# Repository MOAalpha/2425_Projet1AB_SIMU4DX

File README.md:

# 2425_Projet1AB_SIMU4DX
A super nice projet

 L'objectif de ce projet est de reconstituer un simulateur de voiture permettant de ressentir les vraies sensations de conduite, avec un frein à retour de force et 4 pieds movibles.
 
 On s'inspire du projet : https://github.com/ChrGri/DIY-Sim-Racing-FFB-Pedal

 La base ayant déjà été faite, on souhaite modifier le châssis et les pédales de frein afin d'augmenter la sensation de conduire une véritable voiture.

INSTALLER ET FAIRE FONCTIONNER SIMHUB

Tout d'abord, il vous faut installer SimHub sur votre ordinateur.

Cliquez sur "Add/Remove/Features" dans le menu de gauche.

Cliquez sur "addons motion" pour activer le contrôle de mouvement.

Normalement, "Motion" apparaît sur SimHub (icône avec un siège).

Cliquez sur "Let's test it".

Choisissez comme configuration "3 DOFs, 2 fronts, 1 rear".

Cliquez sur "Add new controller".

Choisissez "generic serial output"

Dans "Connexion", assurez-vous que votre carte est connectée sur le bon COM.

Vous pouvez régler la dimension de la plateforme ce qui vous permet d'obtenir la limitation des axes.

Cliquez ensuite sur "Edit serial commands setting".

Dans cet onglet, vous voyez le type de données que SimHub vous envoie : ce sont deux angles (le roll et le pitch) et une translation selon l'axe horizontal qui est appelé "heave".

C'est dans cet onglet que vous pouvez régler la forme des données que vous souhaitez envoyer :

Baudrate: 115000

Data bits: 8

Stop bits: 1

Parity: none

Number of controlled axis: 3

Axis output format: decimal

Axis resolution: 8 bits (donc de 0 à 255)

Motion update commands: <axis1> <axis2> <axis3> (à copier-coller ; vous pouvez aussi cliquer sur les "..." pour les ajouter)

Cliquez sur "Edit axis assignment". Vous n'avez que trois axes (rear center, front left corner, front right corner). Vous pouvez tester l'envoi des données dans cet onglet.

LIRE LES DONNÉES DE SIMHUB

Méthode avec deux STM32 :

Nous avons utilisé cette méthode au début de notre projet, car nous n'avions pas encore terminé l'impression des cartes.

Si vous disposez de deux microcontrôleurs STM32 ayant l'UART 1 et 2, il vous suffit de relier les ports RX, TX et GND de vos deux cartes STM32.

Par la suite, il vous faut installer STM32CubeIDE et PuTTY. Activez l'UART 1 et 2. Puis, ajoutez cette ligne de code qui vous permettra de lire les données.

Une fois que le code est chargé dans les deux cartes, il faut par la suite ouvrir PuTTY et SimHub.

Dans SimHub : Il faut revenir dans l'onglet "Edit axis assignment" et cliquer sur le bouton de test pour que SimHub envoie les données.

Dans PuTTY : Cliquez sur "Connexion type" "Serial", puis choisissez le COM correspondant à votre carte et sélectionnez 115200 bauds.

Méthode avec le hub USB :

Cette méthode permet de tester le fonctionnement du hub USB.

La carte qui reçoit les données est le hub USB dans notre schéma d'architecture ; elle reçoit les données via le port USB. Il faut relier l'un des ports USB du hub USB dédié aux autres cartes vers le PC. Ensuite, vous pourrez lire les données envoyées avec PuTTY. Malheureusement, nous n'avons pas pu le faire, car nous avons rencontré un problème avec le timer de notre microcontrôleur.

 On a effectué une PCB de communication : 
 
 Elle a pour rôle la transmission des infos du jeu prélevés à l'aide de simhub aux 4 moteurs qui font bouger le châssis.

 NB : Le circuit semble correct (On a bien 5V en entrée du régulateur et 3.3V en sortie) MAIS son horloge interne ne fonctionne pas.

 On a effectué une PCB Moteur pour chacun des 4 moteurs : 

Celle-ci se charge d'indiquer au driver à quel point il faut bouger le vérin.

A suivre : 

Tester la PCB du STEPPER pour commander la pédale de frein avec retour de force. \
 \
Assembler le tout. \
Profiter des sensations.

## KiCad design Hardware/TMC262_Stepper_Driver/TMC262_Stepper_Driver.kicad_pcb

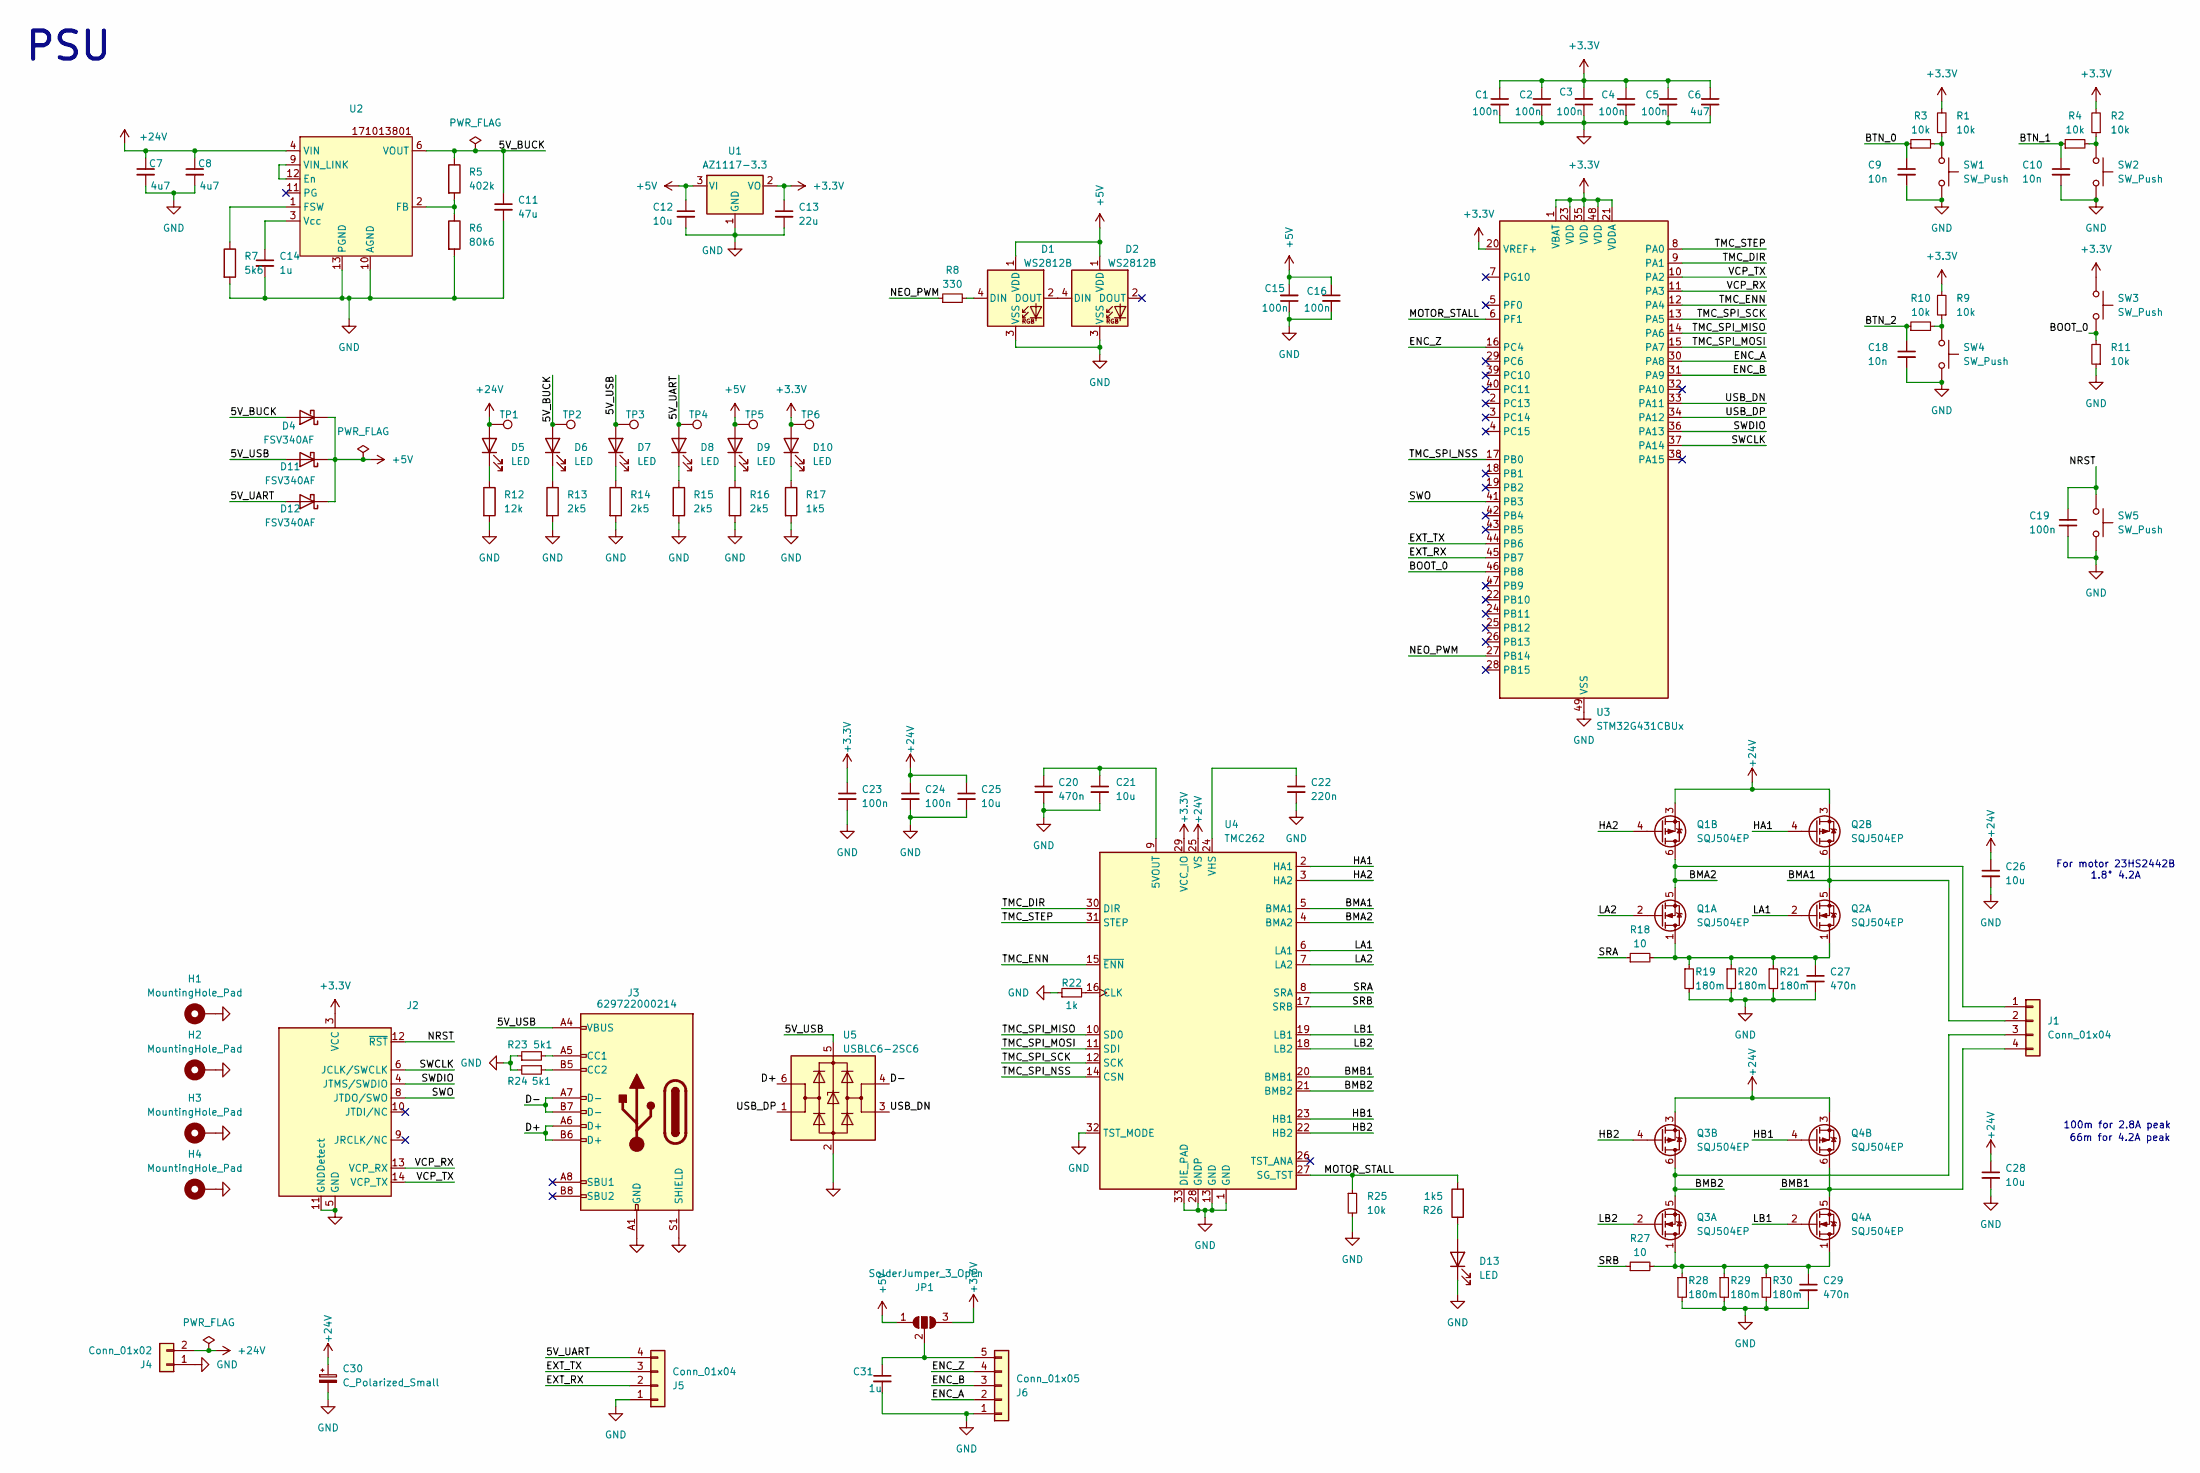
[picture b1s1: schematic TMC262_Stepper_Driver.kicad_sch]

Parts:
C1, C2, C3, C4, C5, C15, C16, C23, C24: 100n; C_0402_1005Metric
C6: 4u7; C_0402_1005Metric
C7, C8: 4u7; C_1210_3225Metric; MPN 885012209048
C9, C10, C18: 10n; C_0402_1005Metric; MPN WE 885012205050
C11: 47u; C_0805_2012Metric; MPN 885 012 107 006
C12, C21: 10u; C_0603_1608Metric; MPN 885 012 106 006
C13: 22u; C_0805_2012Metric; MPN 885 012 107 011
C14, C31: 1u; C_0402_1005Metric
C19: 100n; C_0402_1005Metric; MPN WE 885012205050
C20, C27, C29: 470n; C_0402_1005Metric
C22: 220n; C_0402_1005Metric
C25, C26, C28: 10u; C_1206_3216Metric; MPN 885 012 208 069
C30: C_Polarized_Small; CP_Elec_10x10.5; MPN 865060657012
D1, D2: WS2812B; LED_WS2812B_PLCC4_5.0x5.0mm_P3.2mm
D4, D11, D12: FSV340AF; D_SMA
D5, D6, D7, D8, D9, D10, D13: LED; LED_0603_1608Metric
H1, H2, H3, H4: MountingHole_Pad; MountingHole_3.2mm_M3_Pad_Via
J1: Conn_01x04; JST_XH_B4B-XH-A_1x04_P2.50mm_Vertical
J2: PinHeader_2x07_P1.27mm_Vertical_SMD
J3: 629722000214; USB_C_Receptacle_HRO_TYPE-C-31-M-12; MPN 629722000214
J4: Conn_01x02; AMASS_XT30U-M_1x02_P5.0mm_Vertical
J5: Conn_01x04; JST_PH_B4B-PH-K_1x04_P2.00mm_Vertical
J6: Conn_01x05; JST_PH_B5B-PH-K_1x05_P2.00mm_Vertical
JP1: SolderJumper_3_Open; SolderJumper-3_P2.0mm_Open_TrianglePad1.0x1.5mm
Q1, Q2, Q3, Q4: SQJ504EP; MPN SQJ504EP-T1_GE3
R1, R2, R3, R4, R9, R10, R11, R25: 10k; R_0402_1005Metric
R5: 402k; R_0402_1005Metric
R6: 80k6; R_0402_1005Metric
R7: 5k6; R_0402_1005Metric
R8: 330; R_0402_1005Metric
R12: 12k; R_0402_1005Metric
R13, R14, R15, R16: 2k5; R_0402_1005Metric
R17, R26: 1k5; R_0402_1005Metric
R18, R27: 10; R_0402_1005Metric
R19, R20, R21, R28, R29, R30: 180m; R_0612_1632Metric; MPN 561 070 332 057
R22: 1k; R_0402_1005Metric
R23, R24: 5k1; R_0402_1005Metric
SW1, SW2, SW3, SW4, SW5: SW_Push; KSS221GLFS; MPN KSS221GLFS
TP1: 24V; TestPoint_Pad_D1.0mm
TP2: 5V_BUCK; TestPoint_Pad_D1.0mm
TP3, TP4: 5V_USB; TestPoint_Pad_D1.0mm
TP5: 5V; TestPoint_Pad_D1.0mm
TP6: 3V3; TestPoint_Pad_D1.0mm
U1: AZ1117-3.3; SOT-223
U2: 171013801
U3: STM32G431CBUx; QFN-48-1EP_7x7mm_P0.5mm_EP5.6x5.6mm
U4: TMC262; QFN-32-1EP_5x5mm_P0.5mm_EP3.45x3.45mm
U5: USBLC6-2SC6; SOT-23-6; MPN USBLC6-2SC6

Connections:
+3.3V: C1.1, C2.1, C3.2, C4.1, C5.1, C6.1, C13.1, C23.1, D10.2 (A), J2.3 (VCC), JP1.3 (B), R1.2, R2.2, R9.2, SW3.1, TP6.1, U1.2 (VO), U1.4 (VO), U3.1 (VBAT), U3.20 (VREF+), U3.21 (VDDA), U3.23 (VDD), U3.35 (VDD), U3.48 (VDD), U4.29 (VCC_IO)
+5V: C12.1, C15.2, C16.1, D1.1 (VDD), D2.1 (VDD), D4.1 (K), D9.2 (A), D11.1 (K), D12.1 (K), JP1.1 (A), TP5.1, U1.3 (VI)
+24V: C7.1, C8.1, C24.1, C25.1, C26.1, C28.1, C30.1, D5.2 (A), J4.2, Q1.3 (1), Q2.3 (1), Q3.3 (1), Q4.3 (1), TP1.1, U2.4 (VIN), U2.5 (VIN), U4.25 (VS)
/5V_BUCK: C11.1, D4.2 (A), D6.2 (A), R5.1, TP2.1, U2.6 (VOUT), U2.7 (VOUT)
/5V_UART: D8.2 (A), D12.2 (A), J5.4, TP4.1
/5V_USB: D7.2 (A), D11.2 (A), J3.A4 (VBUS), J3.A9 (VBUS), J3.B4 (VBUS), J3.B9 (VBUS), TP3.1, U5.5 (VBUS)
/BMA1: J1.2, Q2.5 (D), Q2.6 (D), U4.5 (BMA1)
/BMA2: J1.1, Q1.5 (D), Q1.6 (D), U4.4 (BMA2)
/BMB1: J1.4, Q4.5 (D), Q4.6 (D), U4.20 (BMB1)
/BMB2: J1.3, Q3.5 (D), Q3.6 (D), U4.21 (BMB2)
/BOOT_0: R11.2, SW3.2, U3.46 (PB8)
/BTN_0: C9.1, R3.1
/BTN_1: C10.1, R4.1
/BTN_2: C18.1, R10.1
/D+: J3.A6 (D+), J3.B6 (D+), U5.6 (I/O1)
/D-: J3.A7 (D-), J3.B7 (D-), U5.4 (I/O2)
/ENC_A: J6.2, U3.30 (PA8)
/ENC_B: J6.3, U3.31 (PA9)
/ENC_Z: J6.4, U3.16 (PC4)
/EXT_RX: J5.2, U3.45 (PB7)
/EXT_TX: J5.3, U3.44 (PB6)
/HA1: Q2.4 (G), U4.2 (HA1)
/HA2: Q1.4 (G), U4.3 (HA2)
/HB1: Q4.4 (G), U4.23 (HB1)
/HB2: Q3.4 (G), U4.22 (HB2)
/LA1: Q2.2 (G), U4.6 (LA1)
/LA2: Q1.2 (G), U4.7 (LA2)
/LB1: Q4.2 (G), U4.19 (LB1)
/LB2: Q3.2 (G), U4.18 (LB2)
/MOTOR_STALL: R25.1, R26.2, U3.6 (PF1), U4.27 (SG_TST)
/NEO_PWM: R8.1, U3.27 (PB14)
/NRST: C19.1, J2.12 (~RST), SW5.1
/SRA: R18.1, U4.8 (SRA)
/SRB: R27.1, U4.17 (SRB)
/SWCLK: J2.6 (JCLK/SWCLK), U3.37 (PA14)
/SWDIO: J2.4 (JTMS/SWDIO), U3.36 (PA13)
/SWO: J2.8 (JTDO/SWO), U3.41 (PB3)
/TMC_DIR: U3.9 (PA1), U4.30 (DIR)
/TMC_ENN: U3.12 (PA4), U4.15 (~ENN)
/TMC_SPI_MISO: U3.14 (PA6), U4.10 (SD0)
/TMC_SPI_MOSI: U3.15 (PA7), U4.11 (SDI)
/TMC_SPI_NSS: U3.17 (PB0), U4.14 (CSN)
/TMC_SPI_SCK: U3.13 (PA5), U4.12 (SCK)
/TMC_STEP: U3.8 (PA0), U4.31 (STEP)
/USB_DN: U3.33 (PA11), U5.3 (I/O2)
/USB_DP: U3.34 (PA12), U5.1 (I/O1)
/VCP_RX: J2.13 (VCP_RX), U3.11 (PA3)
/VCP_TX: J2.14 (VCP_TX), U3.10 (PA2)
GND: C1.2, C2.2, C3.1, C4.2, C5.2, C6.2, C7.2, C8.2, C9.2, C10.2, C11.2, C12.2, C13.2, C14.2, C15.1, C16.2, C18.2, C19.2, C20.2, C21.2, C22.2, C23.2, C24.2, C25.2, C26.2, C27.2, C28.2, C29.2, C30.2, C31.2, D1.3 (VSS), D2.3 (VSS), D13.1 (K), H1.1, H2.1, H3.1, H4.1, J2.5 (GND), J2.7 (GND), J2.11 (GNDDetect), J3.A1 (GND), J3.A12 (GND), J3.B1 (GND), J3.B12 (GND), J3.S1 (SHIELD), J4.1, J5.1, J6.1, R6.2, R7.2, R11.1, R12.2, R13.2, R14.2, R15.2, R16.2, R17.2, R19.2, R20.2, R21.2, R22.1, R23.1, R24.2, R25.2, R28.2, R29.2, R30.2, SW1.2, SW2.2, SW4.2, SW5.2, U1.1 (GND), U2.10 (AGND), U2.13 (PGND), U3.49 (VSS), U4.1 (GND), U4.13 (GND), U4.28 (GNDP), U4.32 (TST_MODE), U4.33 (DIE_PAD), U5.2 (GND)
unnamed: D1.4 (DIN), R8.2
unnamed: D1.2 (DOUT), D2.4 (DIN)
unnamed: D5.1 (K), R12.1
unnamed: D6.1 (K), R13.1
unnamed: D7.1 (K), R14.1
unnamed: D8.1 (K), R15.1
unnamed: D9.1 (K), R16.1
unnamed: D10.1 (K), R17.1
unnamed: D13.2 (A), R26.1
unnamed: J3.A5 (CC1), R23.2
unnamed: J3.B5 (CC2), R24.1
unnamed: C31.1, J6.5, JP1.2 (C)
unnamed: C27.1, Q1.1 (S), Q2.1 (S), R18.2, R19.1, R20.1, R21.1
unnamed: C29.1, Q3.1 (S), Q4.1 (S), R27.2, R28.1, R29.1, R30.1
unnamed: R1.1, R3.2, SW1.1
unnamed: R2.1, R4.2, SW2.1
unnamed: R9.1, R10.2, SW4.1
unnamed: U2.9 (VIN_LINK), U2.12 (En)
unnamed: R5.2, R6.1, U2.2 (FB)
unnamed: R7.1, U2.1 (FSW)
unnamed: C14.1, U2.3 (Vcc)
unnamed: C20.1, C21.1, U4.9 (5VOUT)
unnamed: R22.2, U4.16 (CLK)
unnamed: C22.1, U4.24 (VHS)

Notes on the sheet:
66m for 4.2A peak
100m for 2.8A peak
For motor 23HS2442B 1.8° 4.2A
PSU

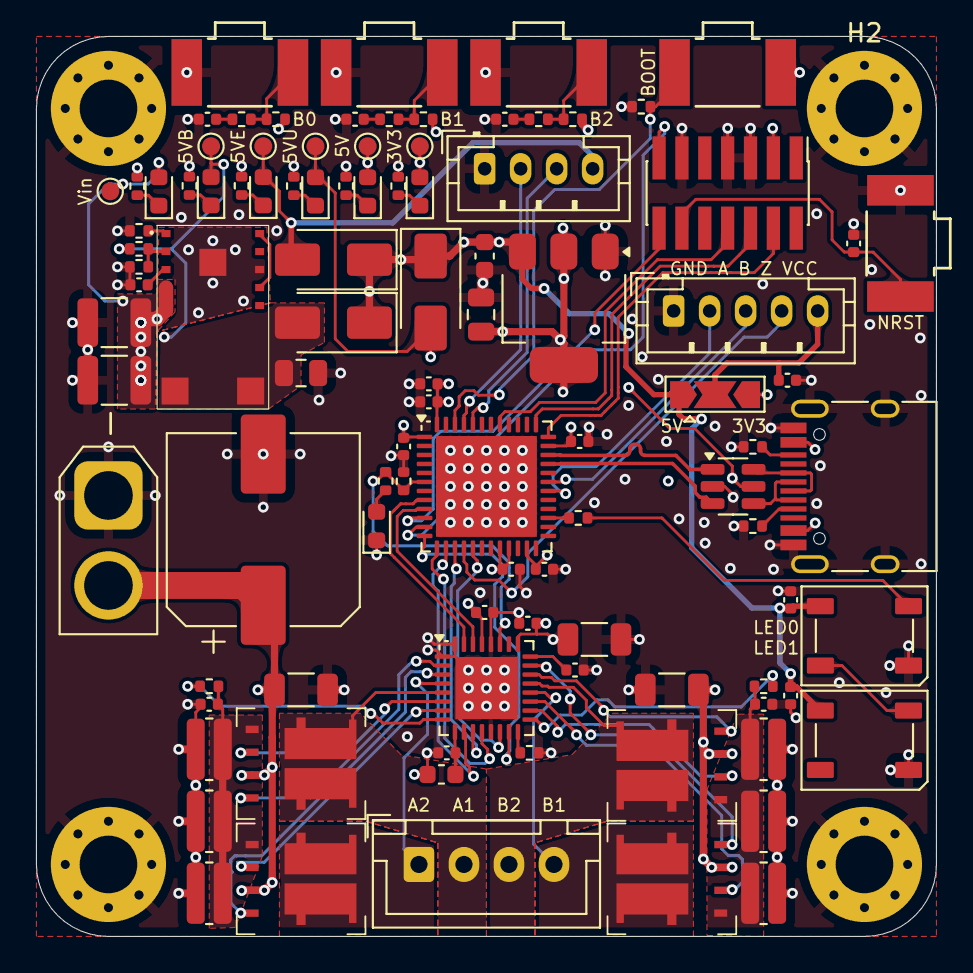
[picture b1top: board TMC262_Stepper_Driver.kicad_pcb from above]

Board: 4 copper layers, 50.0 x 50.0 mm, 103 parts (0 on the bottom side), 73 nets.

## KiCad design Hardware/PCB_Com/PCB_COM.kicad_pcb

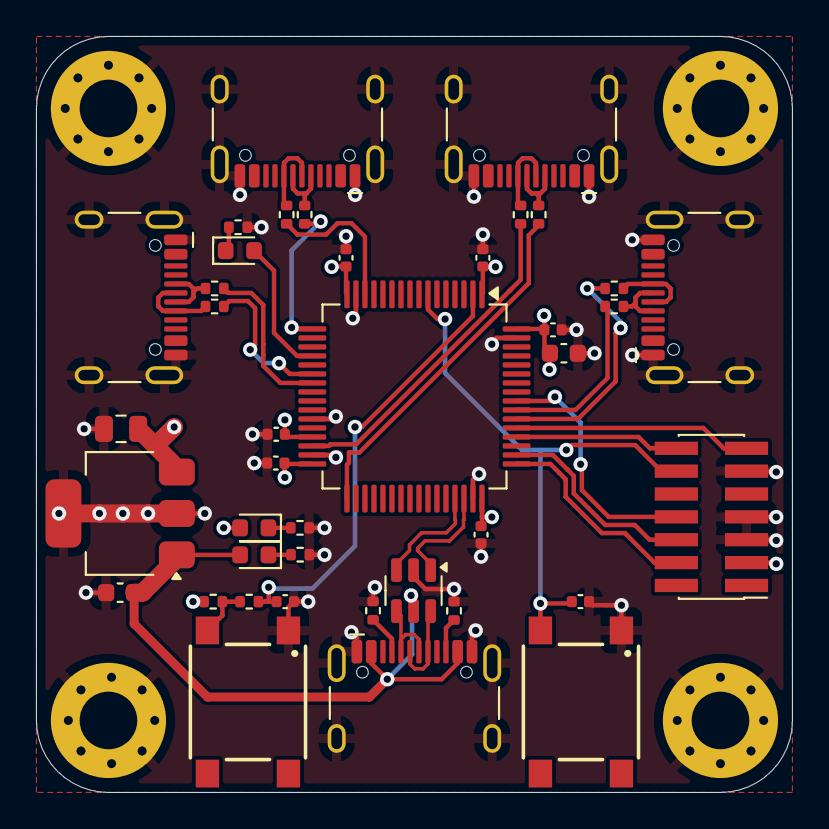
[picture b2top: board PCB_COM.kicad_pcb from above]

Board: 4 copper layers, 42.0 x 42.0 mm, 44 parts (0 on the bottom side), 37 nets.

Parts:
C1: 4u7; C_0603_1608Metric
C2, C3, C4, C6, C7, C8, C9: 100n; C_0402_1005Metric
C5: 10n; C_0402_1005Metric
C10: 10u; C_0603_1608Metric
C11: 22u; C_0805_2012Metric
D1, D3: LED_RED; LED_0603_1608Metric
D2: LED_GREEN; LED_0603_1608Metric
H1, H2, H3, H4: MH; MountingHole_3.2mm_M3_Pad_Via
J1, J2, J4, J5, J6: USB_C_Receptacle_USB2.0_14P; USB_C_Receptacle_HCTL_HC-TYPE-C-16P-01A
J3: 629722000214; PinHeader_2x07_P1.27mm_Vertical_SMD
R1, R2: 10k; R_0402_1005Metric
R3, R12, R13: 1k; R_0402_1005Metric
R4, R5, R6, R7, R8, R9, R10, R11: 330; R_0402_1005Metric
R14, R15: 5k1; R_0402_1005Metric
SW1, SW2: SW_Push; 430152043826
U1: STM32G474RETx; LQFP-64_10x10mm_P0.5mm
U2: AZ1117CH2-3.3TRG1; SOT-223
U3: USBLC6-2SC6; SOT-23-6

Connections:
+3.3V: C1.1, C2.1, C4.1, C6.1, C7.1, C8.1, C9.1, C11.1, D2.2 (A), J3.3 (VCC), R1.1, U1.1 (VBAT), U1.16 (VDD), U1.29 (VDDA), U1.32 (VDD), U1.48 (VDD), U1.64 (VDD), U2.3 (OUTPUT)
+5V: C10.2, D3.2 (A), J6.A4 (VBUS), J6.A9 (VBUS), J6.B4 (VBUS), J6.B9 (VBUS), U2.1 (INPUT), U3.5 (VBUS)
/LED: D1.2 (A), U1.20 (PA6)
D+: J6.A6 (D+), J6.B6 (D+), U3.6 (I/O1)
D-: J6.A7 (D-), J6.B7 (D-), U3.4 (I/O2)
GND: C1.2, C2.2, C3.2, C4.2, C5.2, C6.2, C7.2, C8.2, C9.2, C10.1, C11.2, H1.1, H2.1, H3.1, H4.1, J1.A1 (GND), J1.A12 (GND), J1.B1 (GND), J1.B12 (GND), J1.S1 (SHIELD), J2.A1 (GND), J2.A12 (GND), J2.B1 (GND), J2.B12 (GND), J2.S1 (SHIELD), J3.5 (GND), J3.7 (GND), J3.11 (GNDDetect), J4.A1 (GND), J4.A12 (GND), J4.B1 (GND), J4.B12 (GND), J4.S1 (SHIELD), J5.A1 (GND), J5.A12 (GND), J5.B1 (GND), J5.B12 (GND), J5.S1 (SHIELD), J6.A1 (GND), J6.A12 (GND), J6.B1 (GND), J6.B12 (GND), J6.S1 (SHIELD), R3.2, R12.2, R13.2, R14.1, R15.1, SW1.1, SW2.1, U1.15 (VSS), U1.27 (VSSA), U1.31 (VSS), U1.47 (VSS), U1.63 (VSS), U2.2 (ADJ/GND_1), U2.4 (ADJ/GND_2), U3.2 (GND)
NRST: C3.1, J3.12 (~RST), SW1.2, U1.7 (PG10)
unnamed: D1.1 (K), R3.1
unnamed: D2.1 (K), R12.1
unnamed: D3.1 (K), R13.1
unnamed: J1.A6 (D+), J1.B6 (D+), R5.2
unnamed: J1.A7 (D-), J1.B7 (D-), R4.1
unnamed: J2.A6 (D+), J2.B6 (D+), R7.2
unnamed: J2.A7 (D-), J2.B7 (D-), R6.1
unnamed: J4.A6 (D+), J4.B6 (D+), R9.2
unnamed: J4.A7 (D-), J4.B7 (D-), R8.1
unnamed: J5.A6 (D+), J5.B6 (D+), R11.2
unnamed: J5.A7 (D-), J5.B7 (D-), R10.1
unnamed: J6.A5 (CC1), R14.2
unnamed: J6.B5 (CC2), R15.2
unnamed: R1.2, R2.2, SW2.2
unnamed: C5.1, R2.1, U1.2 (PC13)
SWCLK: J3.6 (JCLK/SWCLK), U1.50 (PA14)
SWDIO: J3.4 (JTMS/SWDIO), U1.49 (PA13)
SWO: J3.8 (JTDO/SWO), U1.56 (PB3)
UART5_RX: R10.2, U1.55 (PD2)
UART5_TX: R11.1, U1.54 (PC12)
USART1_RX: R4.2, U1.23 (PC5)
USART1_TX: R5.1, U1.22 (PC4)
USART2_RX: R6.2, U1.17 (PA3)
USART2_TX: R7.1, U1.14 (PA2)
USART3_RX: R8.2, U1.33 (PB11)
USART3_TX: R9.1, U1.30 (PB10)
USART4_RX: J3.13 (VCP_RX), U1.53 (PC11)
USART4_TX: J3.14 (VCP_TX), U1.52 (PC10)
USB_D+: U1.46 (PA12), U3.1 (I/O1)
USB_D-: U1.45 (PA11), U3.3 (I/O2)

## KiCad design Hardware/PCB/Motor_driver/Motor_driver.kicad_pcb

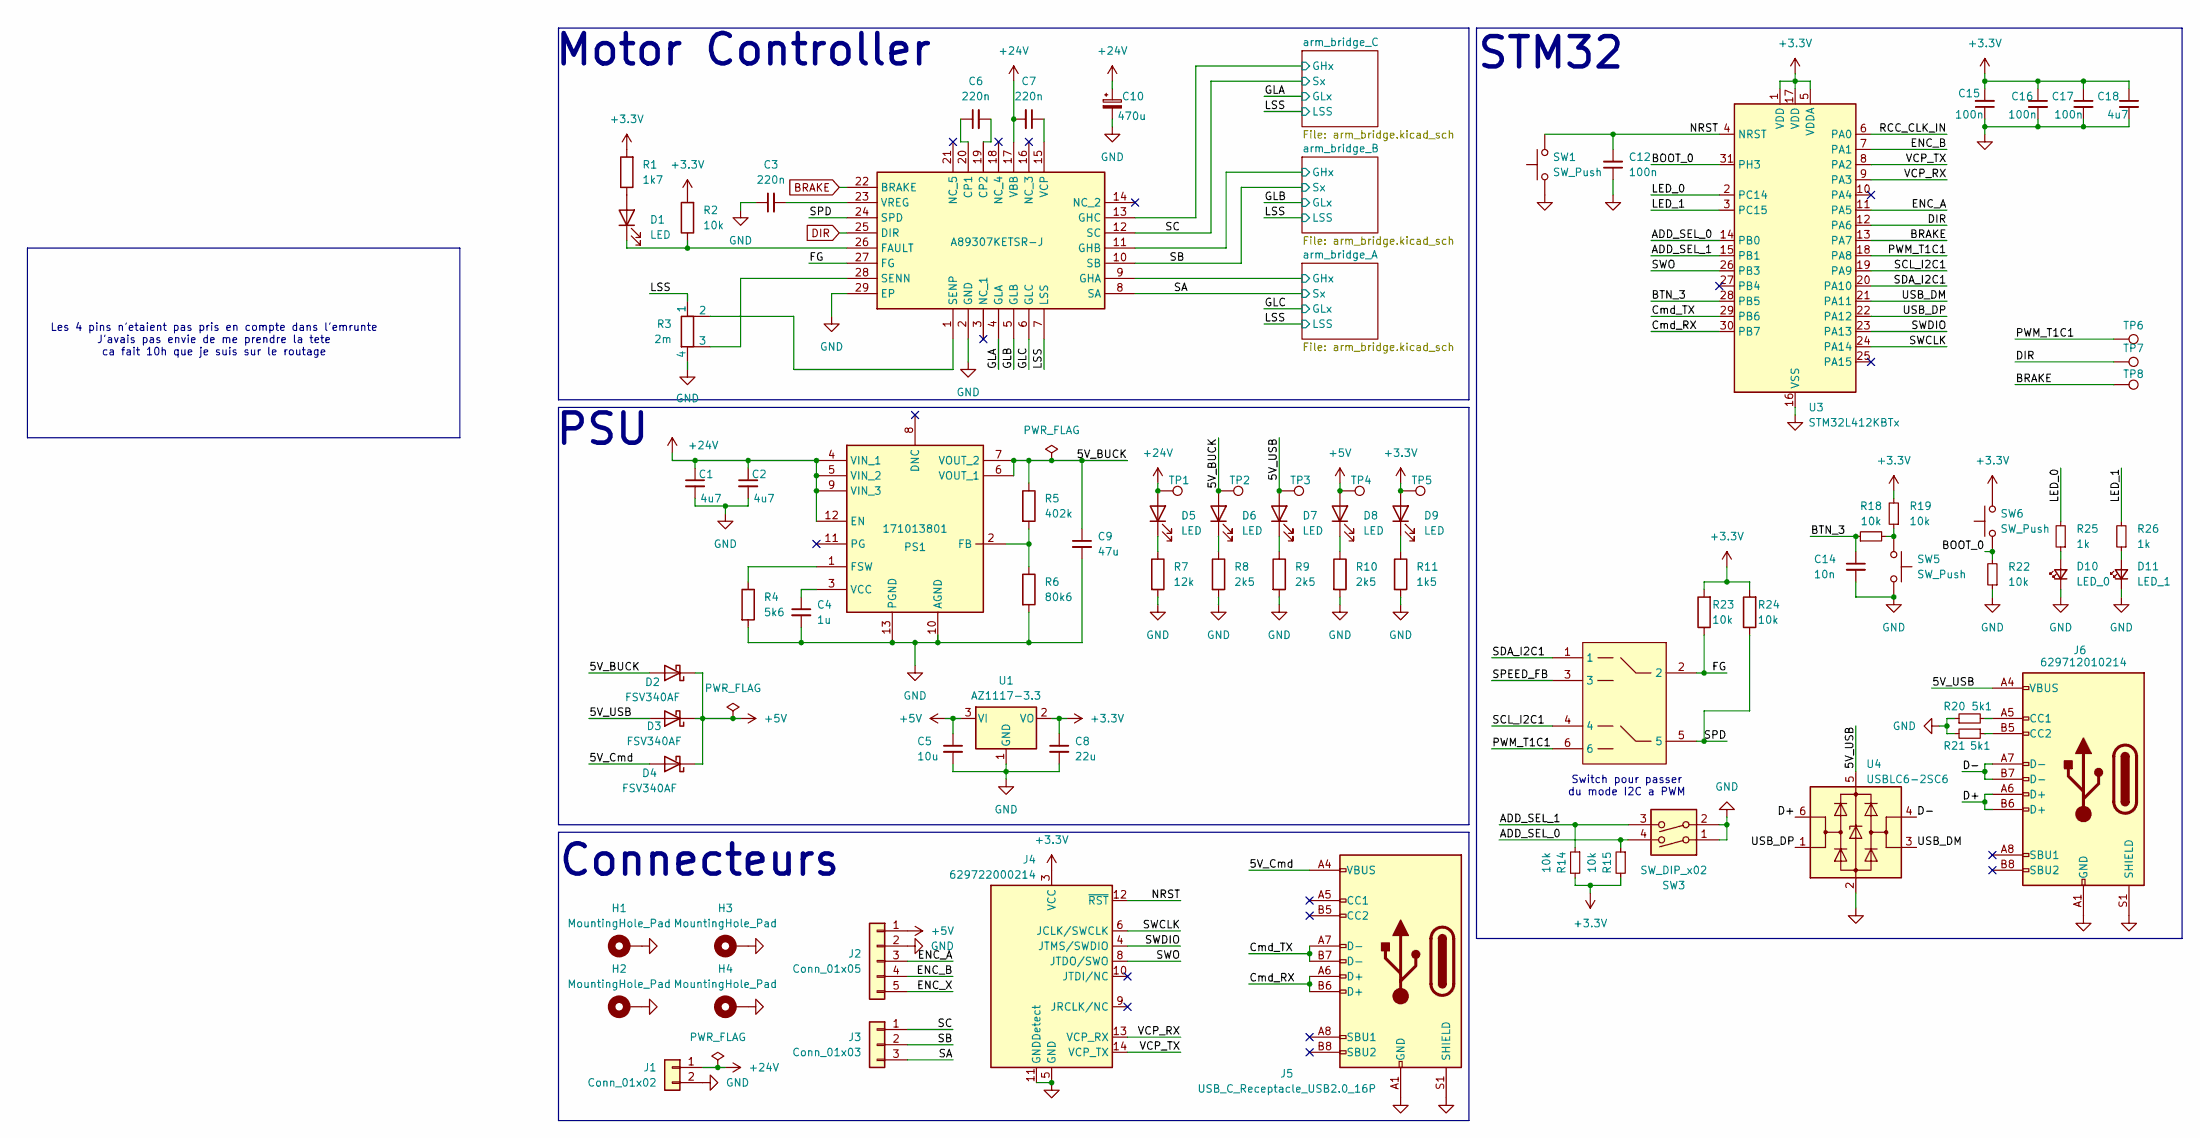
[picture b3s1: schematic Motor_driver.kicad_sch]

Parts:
C1, C2: 4u7; C_1210_3225Metric; MPN 885012209048
C3, C6, C7: 220n; C_0402_1005Metric
C4: 1u; C_0603_1608Metric; MPN 885012207051
C5: 10u; C_0603_1608Metric
C8: 22u; C_0603_1608Metric
C9: 47u; C_0603_1608Metric
C10: 470u; CAPAE1710X1700N
C12, C15, C16, C17: 100n; C_0402_1005Metric
C14: 10n; C_0402_1005Metric; MPN WE 885012205050
C18: 4u7; C_0603_1608Metric
D1: LED; C_0603_1608Metric; MPN 150060RS55040
D2, D3, D4: FSV340AF; D_SMA
D5, D6, D7, D8, D9: LED; LED_0603_1608Metric
D10: LED_0; LED_0603_1608Metric
D11: LED_1; LED_0603_1608Metric
H1, H2, H3, H4: MountingHole_Pad; MountingHole_3.2mm_M3_Pad_Via
IC1: A89307KETSR-J; A8519KETTRR1; Manufacturer_Part_Number A89307KETSR-J; Mouser Part Number 250-A89307KETSR-J
J1: Conn_01x02; AMASS_XT60PW-M_1x02_P7.20mm_Horizontal
J2: Conn_01x05; JST_XH_B5B-XH-A_1x05_P2.50mm_Vertical
J3: Conn_01x03; PhoenixContact_GMSTBVA_2,5_3-G-7,62_1x03_P7.62mm_Vertical
J4: 629722000214; PinHeader_2x07_P1.27mm_Vertical_SMD
J5: USB_C_Receptacle_USB2.0_16P; USB_C_Receptacle_HCTL_HC-TYPE-C-16P-01A
J6: 629712010214; USB_C_Receptacle_GCT_USB4115-03-C
PS1: 171013801; Manufacturer_Part_Number 171013801; Mouser Part Number 710-171013801
R1: 1k7; R_0402_1005Metric
R2, R14, R15, R18, R19, R22, R23, R24: 10k; R_0402_1005Metric
R3: 2m; R_Shunt_Ohmite_LVK24
R4: 5k6; R_0402_1005Metric
R5: 402k; R_0402_1005Metric
R6: 80k6; R_0402_1005Metric
R7: 12k; R_0402_1005Metric
R8, R9, R10: 2k5; R_0402_1005Metric
R11: 1k5; R_0402_1005Metric
R20, R21: 5k1; R_0402_1005Metric
R25, R26: 1k; R_0402_1005Metric
SW1: SW_Push; 430152043826
SW3: SW_DIP_x02; 418121270802; MPN 418121270802
SW5, SW6: SW_Push; 430152043826; MPN WE 430182070816
TP1: 24V; TestPoint_Pad_D1.0mm
TP2: 5V_BUCK; TestPoint_Pad_D1.0mm
TP3: 5V_USB; TestPoint_Pad_D1.0mm
TP4: 5V; TestPoint_Pad_D1.0mm
TP5: 3V3; TestPoint_Pad_D1.0mm
TP6: PWM; TestPoint_Pad_D1.0mm
TP7: DIR; TestPoint_Pad_D1.0mm
TP8: BRAKE; TestPoint_Pad_D1.0mm
U1: AZ1117-3.3; SOT-223
U2: 452406020024
U3: STM32L412KBTx; LQFP-32_7x7mm_P0.8mm
U4: USBLC6-2SC6; SOT-23-6

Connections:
+3.3V: C8.1, C15.2, C16.1, C17.1, C18.1, D9.2 (A), J4.3 (VCC), R1.2, R2.2, R14.2, R15.2, R19.2, R23.2, R24.2, SW6.2, TP5.1, U1.2 (VO), U1.4 (VO), U3.1 (VDD), U3.5 (VDDA), U3.17 (VDD); also elsewhere on the board
+5V: C5.1, D2.1 (K), D3.1 (K), D4.1 (K), D8.2 (A), J2.1, TP4.1, U1.3 (VI); also elsewhere on the board
+24V: C1.1, C2.1, C7.2, C10.1, D5.2 (A), IC1.17 (VBB), J1.1, PS1.4 (VIN_1), PS1.5 (VIN_2), PS1.9 (VIN_3), PS1.12 (EN), TP1.1; also elsewhere on the board
/5V_BUCK: C9.1, D2.2 (A), D6.2 (A), PS1.6 (VOUT_1), PS1.7 (VOUT_2), R5.1, TP2.1; also elsewhere on the board
/5V_Cmd: D4.2 (A), J5.A4 (VBUS), J5.A9 (VBUS), J5.B4 (VBUS), J5.B9 (VBUS)
/5V_USB: D3.2 (A), D7.2 (A), J6.A4 (VBUS), J6.A9 (VBUS), J6.B4 (VBUS), J6.B9 (VBUS), TP3.1, U4.5 (VBUS); also elsewhere on the board
/ADD_SEL_0: R15.1, SW3.4, U3.14 (PB0)
/ADD_SEL_1: R14.1, SW3.3, U3.15 (PB1)
/BOOT_0: R22.2, SW6.1, U3.31 (PH3)
/BTN_3: C14.1, R18.1, U3.28 (PB5)
/Cmd_RX: J5.A6 (D+), J5.B6 (D+), U3.30 (PB7)
/Cmd_TX: J5.A7 (D-), J5.B7 (D-), U3.29 (PB6)
/D+: J6.A6 (D+), J6.B6 (D+), U4.6 (I/O1)
/D-: J6.A7 (D-), J6.B7 (D-), U4.4 (I/O2)
/ENC_A: J2.3, U3.11 (PA5)
/ENC_B: J2.4, U3.7 (PA1)
/ENC_X: J2.5
/FG: IC1.27 (FG), R23.1, U2.2
/GLA: IC1.4 (GLA); also elsewhere on the board
/GLB: IC1.5 (GLB); also elsewhere on the board
/GLC: IC1.6 (GLC); also elsewhere on the board
/LED_0: R25.2, U3.2 (PC14)
/LED_1: R26.2, U3.3 (PC15)
/LSS: IC1.7 (LSS), R3.1; also elsewhere on the board
/NRST: C12.2, J4.12 (~RST), SW1.2, U3.4 (NRST)
/PWM_T1C1: TP6.1, U2.6, U3.18 (PA8); also elsewhere on the board
/RCC_CLK_IN: U3.6 (PA0)
/SA: IC1.8 (SA), J3.3; also elsewhere on the board
/SB: IC1.10 (SB), J3.2; also elsewhere on the board
/SC: IC1.12 (SC), J3.1; also elsewhere on the board
/SCL_I2C1: U2.4, U3.19 (PA9)
/SDA_I2C1: U2.1, U3.20 (PA10)
/SPD: IC1.24 (SPD), R24.1, U2.5
/SPEED_FB: U2.3
/SWCLK: J4.6 (JCLK/SWCLK), U3.24 (PA14)
/SWDIO: J4.4 (JTMS/SWDIO), U3.23 (PA13)
/SWO: J4.8 (JTDO/SWO), U3.26 (PB3)
/USB_DM: U3.21 (PA11), U4.3 (I/O2)
/USB_DP: U3.22 (PA12), U4.1 (I/O1)
/VCP_RX: J4.13 (VCP_RX), U3.9 (PA3)
/VCP_TX: J4.14 (VCP_TX), U3.8 (PA2)
/arm_bridge_A/GHx: IC1.9 (GHA); also elsewhere on the board
/arm_bridge_B/GHx: IC1.11 (GHB); also elsewhere on the board
/arm_bridge_C/GHx: IC1.13 (GHC); also elsewhere on the board
BRAKE: IC1.22 (BRAKE), TP8.1, U3.13 (PA7); also elsewhere on the board
DIR: IC1.25 (DIR), TP7.1, U3.12 (PA6); also elsewhere on the board
GND: C1.2, C2.2, C3.1, C4.2, C5.2, C8.2, C9.2, C10.2, C12.1, C14.2, C15.1, C16.2, C17.2, C18.2, D10.1 (K), D11.1 (K), H1.1, H2.1, H3.1, H4.1, IC1.2 (GND), IC1.29 (EP), J1.2, J2.2, J4.5 (GND), J4.7 (GND), J4.11 (GNDDetect), J5.A1 (GND), J5.A12 (GND), J5.B1 (GND), J5.B12 (GND), J5.S1 (SHIELD), J6.A1 (GND), J6.A12 (GND), J6.B1 (GND), J6.B12 (GND), J6.S1 (SHIELD), PS1.10 (AGND), PS1.13 (PGND), R3.4, R4.2, R6.2, R7.2, R8.2, R9.2, R10.2, R11.2, R20.1, R21.2, R22.1, SW1.1, SW3.1, SW3.2, SW5.2, U1.1 (GND), U3.16 (VSS), U3.32 (VSS), U4.2 (GND); also elsewhere on the board
unnamed: D1.2 (A), R1.1
unnamed: D1.1 (K), IC1.26 (FAULT), R2.1
unnamed: D5.1 (K), R7.1
unnamed: D6.1 (K), R8.1
unnamed: D7.1 (K), R9.1
unnamed: D8.1 (K), R10.1
unnamed: D9.1 (K), R11.1
unnamed: D10.2 (A), R25.1
unnamed: D11.2 (A), R26.1
unnamed: C6.1, IC1.20 (CP1)
unnamed: C6.2, IC1.19 (CP2)
unnamed: IC1.28 (SENN), R3.3
unnamed: IC1.1 (SENP), R3.2
unnamed: C7.1, IC1.15 (VCP)
unnamed: C3.2, IC1.23 (VREG)
unnamed: J6.A5 (CC1), R20.2
unnamed: J6.B5 (CC2), R21.1
unnamed: PS1.2 (FB), R5.2, R6.1
unnamed: PS1.1 (FSW), R4.1
unnamed: C4.1, PS1.3 (VCC)
unnamed: R18.2, R19.1, SW5.1

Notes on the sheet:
STM32
PSU
Switch pour passer du mode I2C a PWM
Les 4 pins n'etaient pas pris en compte dans l'emrunte J'avais pas envie de me prendre la tete ca fait 10h que je suis sur le routage
Connecteurs
Motor Controller

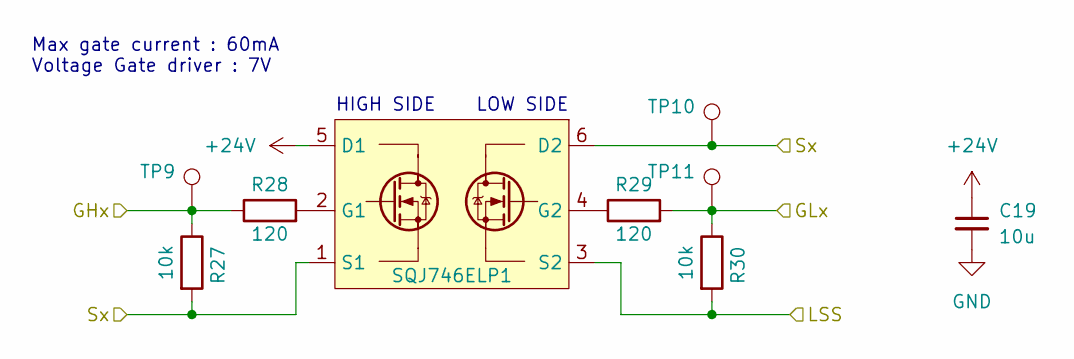
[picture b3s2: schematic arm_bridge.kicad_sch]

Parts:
C19: 10u; C_2220_5750Metric; MPN 885012214001
R27, R30: 10k; R_0402_1005Metric
R28, R29: 120; R_1210_3225Metric
SQJ746ELP1: PowerPAK_SO-8_Dual
TP9, TP10, TP11: GATE C; TestPoint_Pad_D1.0mm

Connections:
+24V: C19.1, SQJ746ELP1.5 (D1); also elsewhere on the board
/GLC: R29.2, R30.1, TP11.1; also elsewhere on the board
/LSS: R30.2, SQJ746ELP1.3 (S2); also elsewhere on the board
/SA: R27.2, SQJ746ELP1.1 (S1), SQJ746ELP1.6 (D2); also elsewhere on the board
/arm_bridge_A/GHx: R27.1, R28.1, TP9.1; also elsewhere on the board
GND: C19.2; also elsewhere on the board
unnamed: R28.2, SQJ746ELP1.2 (G1)
unnamed: R29.1, SQJ746ELP1.4 (G2)

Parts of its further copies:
C20, C21: 10u; C_2220_5750Metric; MPN 885012214001
R31, R34, R35, R38: 10k; R_0402_1005Metric
R32, R33, R36, R37: 120; R_1210_3225Metric
SQJ746ELP2, SQJ746ELP3: PowerPAK_SO-8_Dual

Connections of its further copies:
+24V: C20.1, C21.1, SQJ746ELP2.5 (D1), SQJ746ELP3.5 (D1); also elsewhere on the board
/GLA: R37.2, R38.1; also elsewhere on the board
/GLB: R33.2, R34.1; also elsewhere on the board
/LSS: R34.2, R38.2, SQJ746ELP2.3 (S2), SQJ746ELP3.3 (S2); also elsewhere on the board
/SB: R31.2, SQJ746ELP2.1 (S1), SQJ746ELP2.6 (D2); also elsewhere on the board
/SC: R35.2, SQJ746ELP3.1 (S1), SQJ746ELP3.6 (D2); also elsewhere on the board
/arm_bridge_B/GHx: R31.1, R32.1; also elsewhere on the board
/arm_bridge_C/GHx: R35.1, R36.1; also elsewhere on the board
GND: C20.2, C21.2; also elsewhere on the board
unnamed: R32.2, SQJ746ELP2.2 (G1)
unnamed: R33.1, SQJ746ELP2.4 (G2)
unnamed: R36.2, SQJ746ELP3.2 (G1)
unnamed: R37.1, SQJ746ELP3.4 (G2)

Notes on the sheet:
HIGH SIDE
LOW SIDE
Max gate current : 60mA Voltage Gate driver : 7V

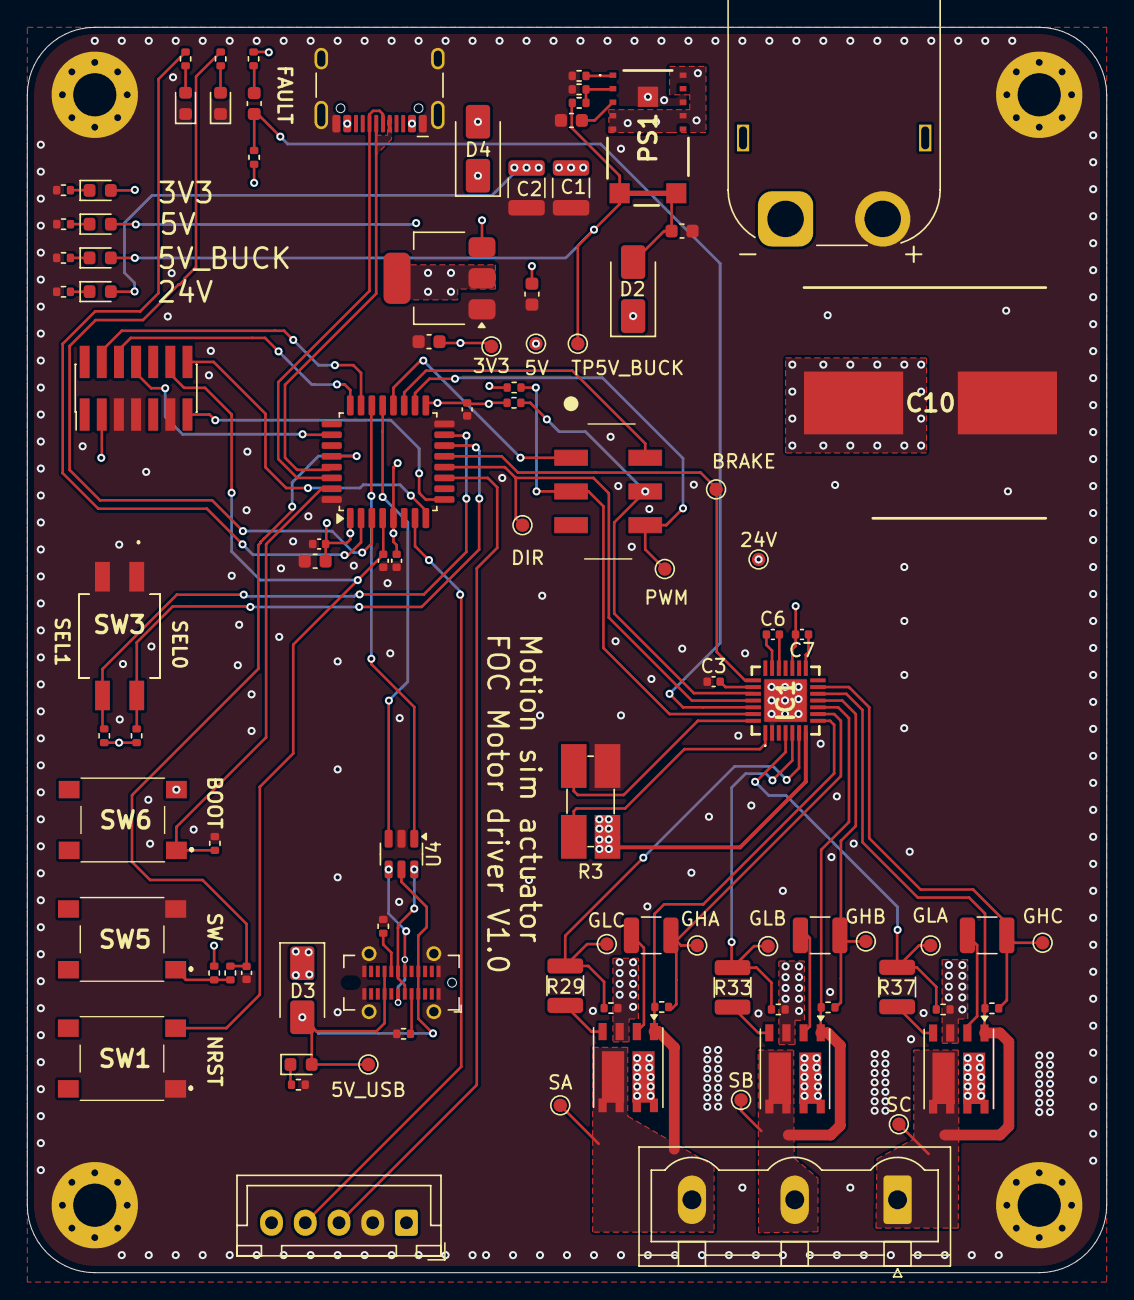
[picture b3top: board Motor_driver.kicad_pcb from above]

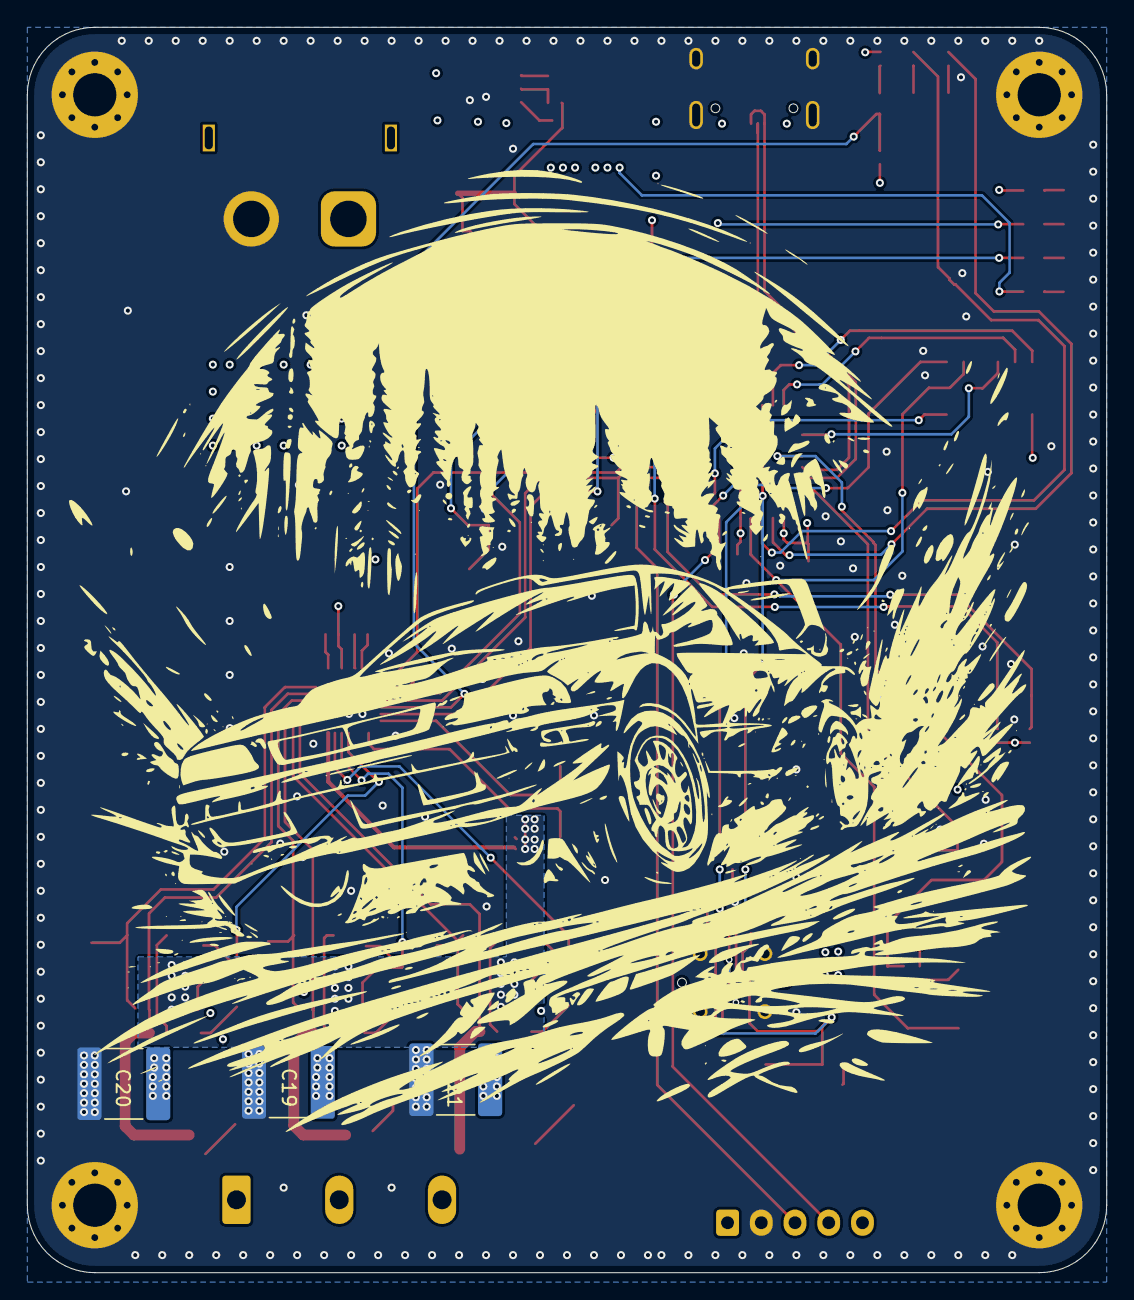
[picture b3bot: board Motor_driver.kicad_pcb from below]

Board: 4 copper layers, 80.0 x 92.3 mm, 104 parts (3 on the bottom side), 71 nets.

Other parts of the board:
3V3: 3V3; TestPoint_Pad_D1.0mm
5V: 5V; TestPoint_Pad_D1.0mm
5V_USB: 5V_USB; TestPoint_Pad_D1.0mm
24V: 24V; TestPoint_Pad_D1.0mm
BRAKE: BRAKE; TestPoint_Pad_D1.0mm
DIR: DIR; TestPoint_Pad_D1.0mm
GHB: GATE C; TestPoint_Pad_D1.0mm
GHC: GATE C; TestPoint_Pad_D1.0mm
GLA: GATE C; TestPoint_Pad_D1.0mm
GLB: GATE C; TestPoint_Pad_D1.0mm
PWM: PWM; TestPoint_Pad_D1.0mm
SA: GATE C; TestPoint_Pad_D1.0mm
SB: GATE C; TestPoint_Pad_D1.0mm
SC: GATE C; TestPoint_Pad_D1.0mm
TP5V_BUCK: 5V_BUCK; TestPoint_Pad_D1.0mm

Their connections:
+3.3V: 3V3.1; also elsewhere on the board
+5V: 5V.1; also elsewhere on the board
+24V: 24V.1; also elsewhere on the board
/5V_BUCK: TP5V_BUCK.1; also elsewhere on the board
/5V_USB: 5V_USB.1; also elsewhere on the board
/GLA: GLA.1; also elsewhere on the board
/GLB: GLB.1; also elsewhere on the board
/PWM_T1C1: PWM.1; also elsewhere on the board
/SA: SA.1; also elsewhere on the board
/SB: SB.1; also elsewhere on the board
/SC: SC.1; also elsewhere on the board
/arm_bridge_B/GHx: GHB.1; also elsewhere on the board
/arm_bridge_C/GHx: GHC.1; also elsewhere on the board
BRAKE: BRAKE.1; also elsewhere on the board
DIR: DIR.1; also elsewhere on the board
